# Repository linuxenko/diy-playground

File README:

Yet another bunch of example applications and information about avr programming.
===============================================================================

I've decided to gather everything that interested me in avr programming
inside of a single repository to share it. While I'm learning different
techniques and tricks playing around with avr, the repository is going to grow.

Table of contents
===============================================================================

I'm trying to provide every application with short description in README file,
as well, an information could be provided inside of its source code files.

  documentation  This folder contains some related documentation and things I'm unable to remember, so, now it
  is the place to search instead of making another web search request.

  74hc164     A very basic implementation of "shiftOut" for AVR with example.
  blink-int   The same application using avr timer with interruption.
  blink-timer Custom timer countdown check inside of main loop.
  blink       General "hello world" application for microcontrollers in particular for an avr controller.
  buttons     Button related examples
  pcm-sound   Example of an avr timer usage to play sound using nothing but Mk.
  uart        Serial communication techniques and examples
  usb-pcm     Plays stream (actualy sound data) via usb.

Notes about "electronics" and "documentation" folders:
 Nothing yet

Notes
===============================================================================

Makefiles were borrowed form the v-usb project, they have to be configured for an
exact hardware you're intended to build it for (device type, oscillator frequency,
fuses and maybe avrdude's staff to make "make program" work properly").

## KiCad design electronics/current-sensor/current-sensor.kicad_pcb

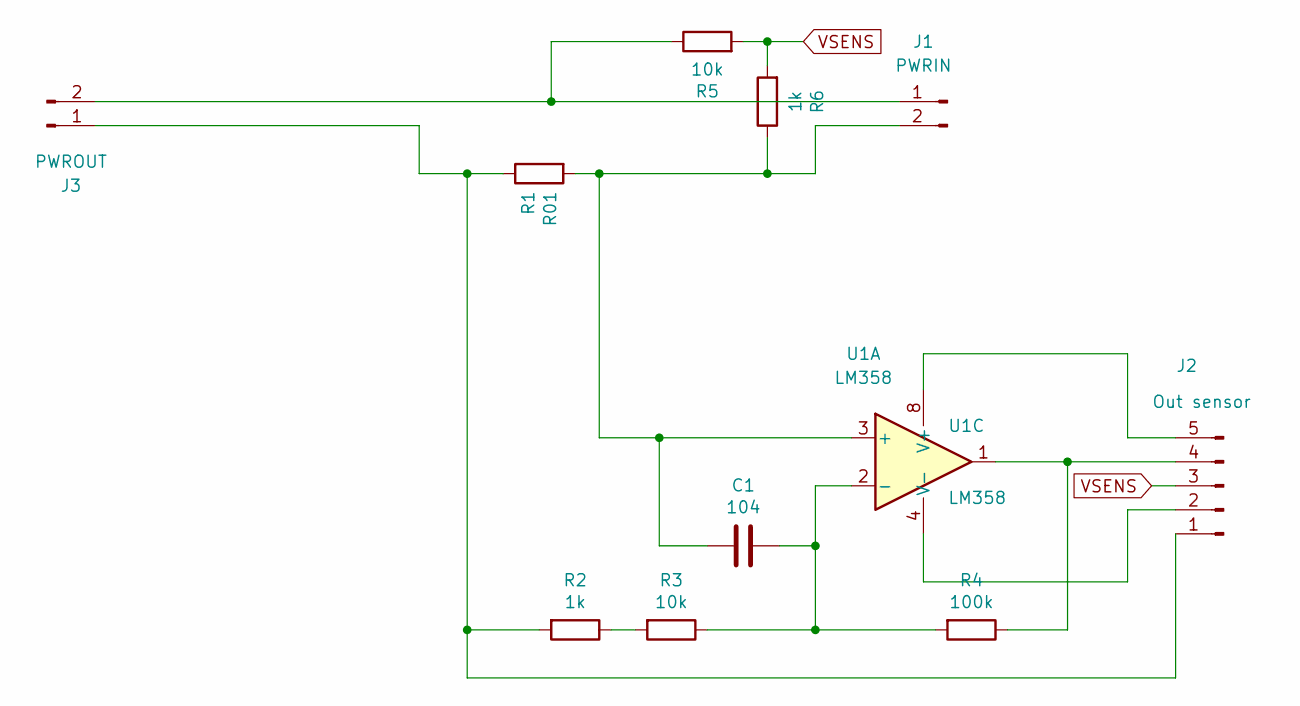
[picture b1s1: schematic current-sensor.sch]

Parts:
C1: 104; C_Disc_D4.3mm_W1.9mm_P5.00mm
J1: PWRIN; PhoenixContact_MCV_1,5_2-G-5.08_1x02_P5.08mm_Vertical
J2: Out sensor; PinHeader_1x05_P2.54mm_Vertical
J3: PWROUT; PhoenixContact_MCV_1,5_2-G-5.08_1x02_P5.08mm_Vertical
R1: R01; R_Axial_DIN0207_L6.3mm_D2.5mm_P10.16mm_Horizontal
R2, R6: 1k; R_Axial_DIN0204_L3.6mm_D1.6mm_P7.62mm_Horizontal
R3, R5: 10k; R_Axial_DIN0204_L3.6mm_D1.6mm_P7.62mm_Horizontal
R4: 100k; R_Axial_DIN0204_L3.6mm_D1.6mm_P7.62mm_Horizontal
U1: LM358; SO-8_5.3x6.2mm_P1.27mm

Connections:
unnamed: C1.1, R3.1, R4.2, U1.2 (-)
unnamed: C1.2, J1.2, R1.2, R6.1, U1.3 (+)
unnamed: J1.1, J3.2, R5.1
unnamed: J2.1, J3.1, R1.1, R2.2
unnamed: J2.2, U1.4 (V-)
unnamed: J2.4, R4.1, U1.1
unnamed: J2.5, U1.8 (V+)
unnamed: R2.1, R3.2
VSENS: J2.3, R5.2, R6.2

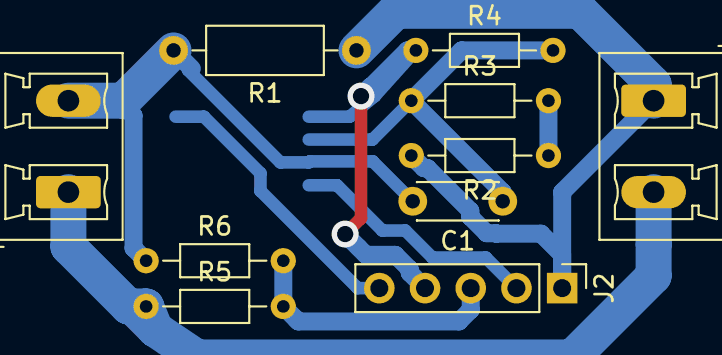
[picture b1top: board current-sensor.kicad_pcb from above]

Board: 2 copper layers, 11 parts (1 on the bottom side), 9 nets.

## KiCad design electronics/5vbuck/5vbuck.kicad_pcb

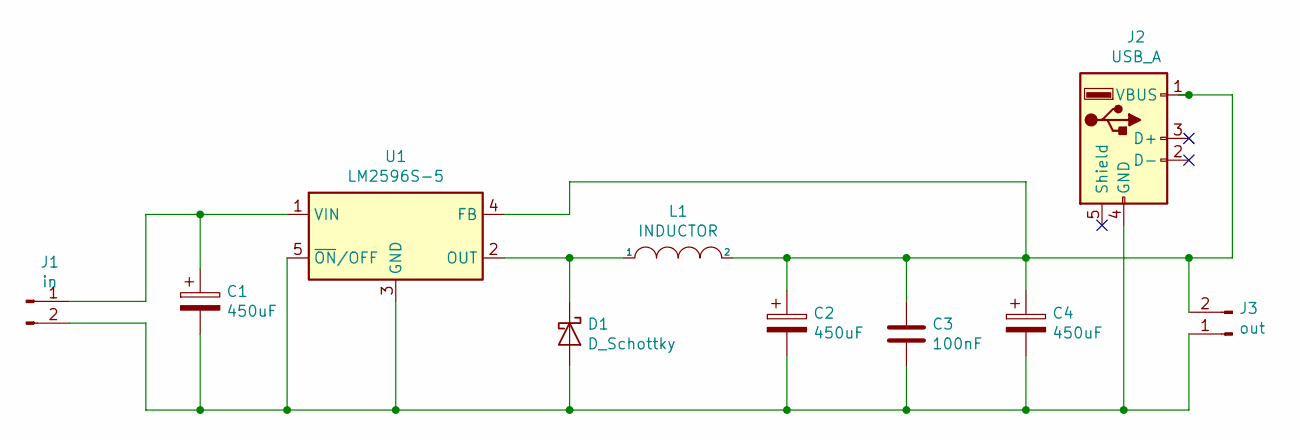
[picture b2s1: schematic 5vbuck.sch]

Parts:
C1, C2, C4: 450uF; CP_Radial_D8.0mm_P5.00mm
C3: 100nF; C_Disc_D4.3mm_W1.9mm_P5.00mm
D1: D_Schottky; D_DO-15_P15.24mm_Horizontal
J1: in; PhoenixContact_MCV_1,5_2-G-5.08_1x02_P5.08mm_Vertical
J2: USB_A; USB_A_Stewart_SS-52100-001_Horizontal
J3: out; PhoenixContact_MCV_1,5_2-G-5.08_1x02_P5.08mm_Vertical
L1: INDUCTOR; L_Toroid_Horizontal_D7.8mm_P13.00mm_Diameter9-5mm_Amidon-T30
U1: LM2596S-5; TO-263-5_TabPin3

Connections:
unnamed: C1.1, J1.1, U1.1 (VIN)
unnamed: C1.2, C2.2, C3.2, C4.2, D1.2 (A), J1.2, J2.4 (GND), J3.1, U1.3 (GND), U1.5 (~ON~/OFF)
unnamed: C2.1, C3.1, C4.1, J2.1 (VBUS), J3.2, L1.2, U1.4 (FB)
unnamed: D1.1 (K), L1.1, U1.2 (OUT)

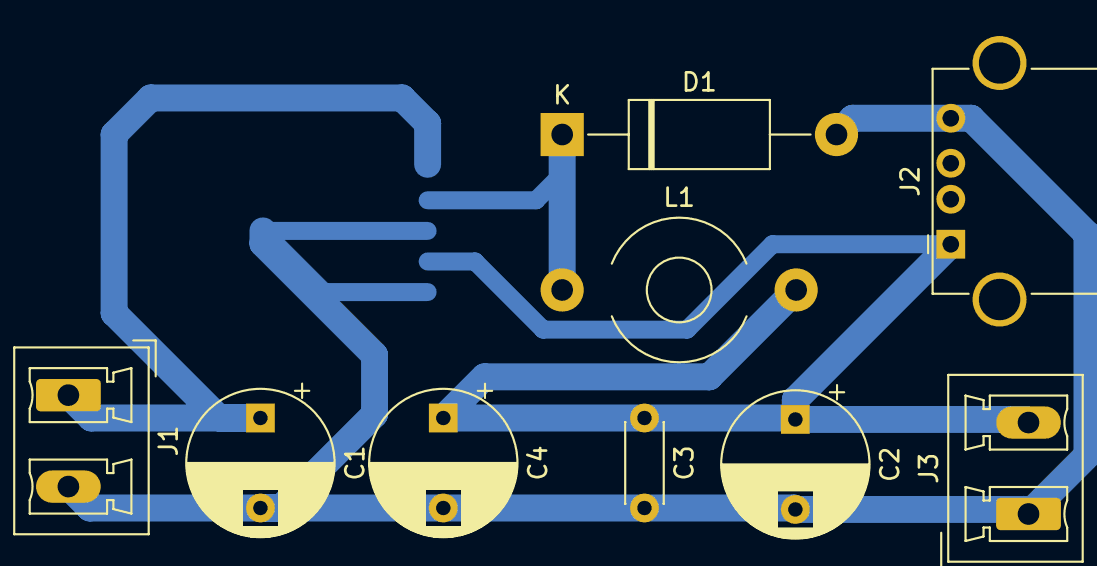
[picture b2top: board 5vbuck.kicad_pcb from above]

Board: 2 copper layers, 10 parts (1 on the bottom side), 4 nets.

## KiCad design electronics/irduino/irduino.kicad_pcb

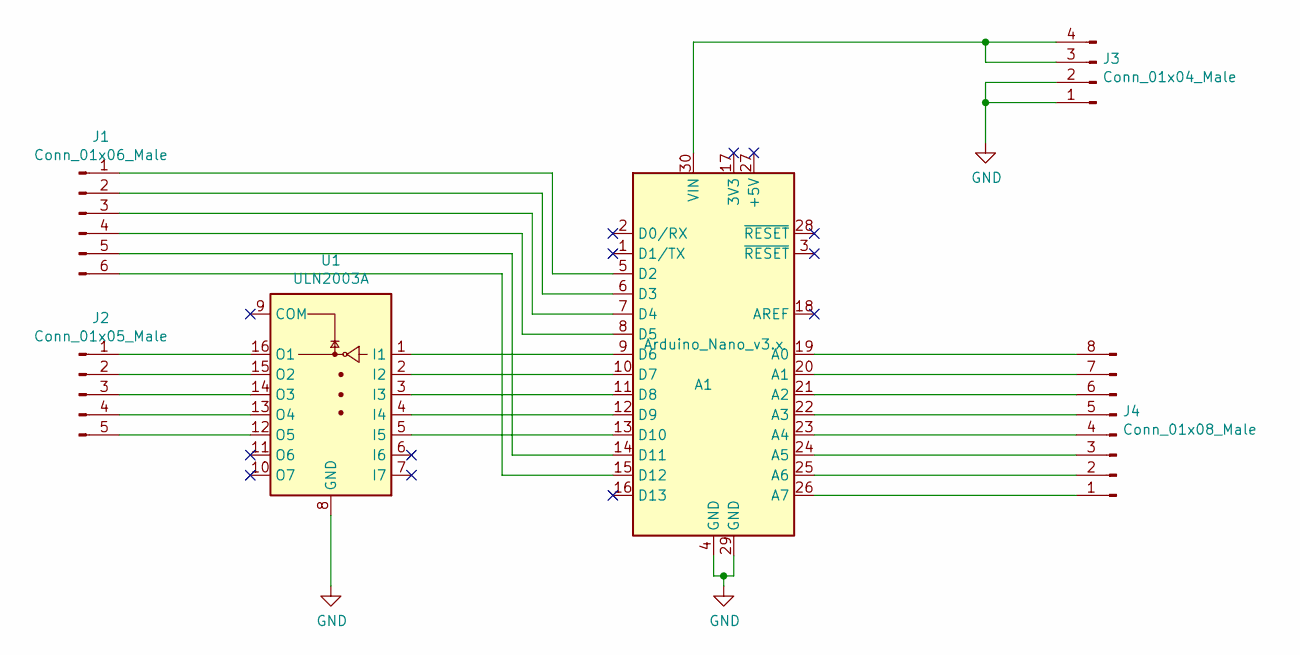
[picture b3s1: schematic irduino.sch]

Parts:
A1: Arduino_Nano_v3.x; Arduino_Nano
J1: Conn_01x06_Male; PinHeader_1x06_P2.54mm_Vertical
J2: Conn_01x05_Male; PinHeader_1x05_P2.54mm_Vertical
J3: Conn_01x04_Male; PinHeader_1x04_P2.54mm_Vertical
J4: Conn_01x08_Male; PinHeader_1x08_P2.54mm_Vertical
U1: ULN2003A; SOIC-16_4.55x10.3mm_P1.27mm

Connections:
GND: A1.4 (GND), A1.29 (GND), J3.1, J3.2, U1.8 (GND)
unnamed: A1.5 (D2), J1.1
unnamed: A1.6 (D3), J1.2
unnamed: A1.7 (D4), J1.3
unnamed: A1.8 (D5), J1.4
unnamed: A1.9 (D6), U1.1 (I1)
unnamed: A1.10 (D7), U1.2 (I2)
unnamed: A1.11 (D8), U1.3 (I3)
unnamed: A1.12 (D9), U1.4 (I4)
unnamed: A1.13 (D10), U1.5 (I5)
unnamed: A1.14 (D11), J1.5
unnamed: A1.15 (D12), J1.6
unnamed: A1.19 (A0), J4.8
unnamed: A1.20 (A1), J4.7
unnamed: A1.21 (A2), J4.6
unnamed: A1.22 (A3), J4.5
unnamed: A1.23 (A4), J4.4
unnamed: A1.24 (A5), J4.3
unnamed: A1.25 (A6), J4.2
unnamed: A1.26 (A7), J4.1
unnamed: A1.30 (VIN), J3.3, J3.4
unnamed: J2.1, U1.16 (O1)
unnamed: J2.2, U1.15 (O2)
unnamed: J2.3, U1.14 (O3)
unnamed: J2.4, U1.13 (O4)
unnamed: J2.5, U1.12 (O5)

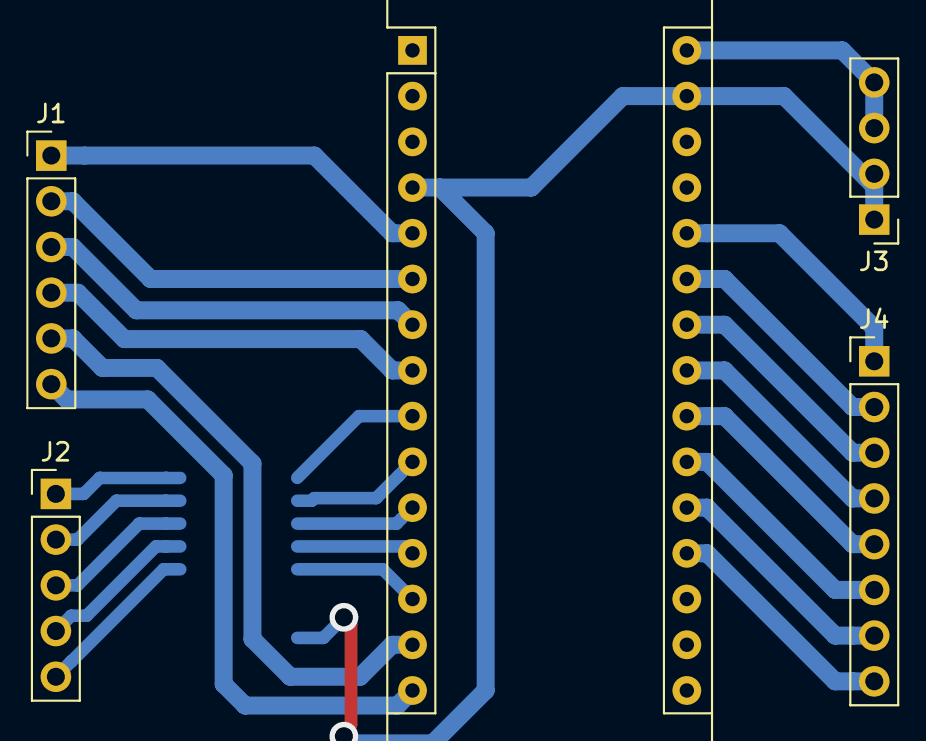
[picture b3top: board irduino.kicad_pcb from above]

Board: 2 copper layers, 6 parts (1 on the bottom side), 26 nets.

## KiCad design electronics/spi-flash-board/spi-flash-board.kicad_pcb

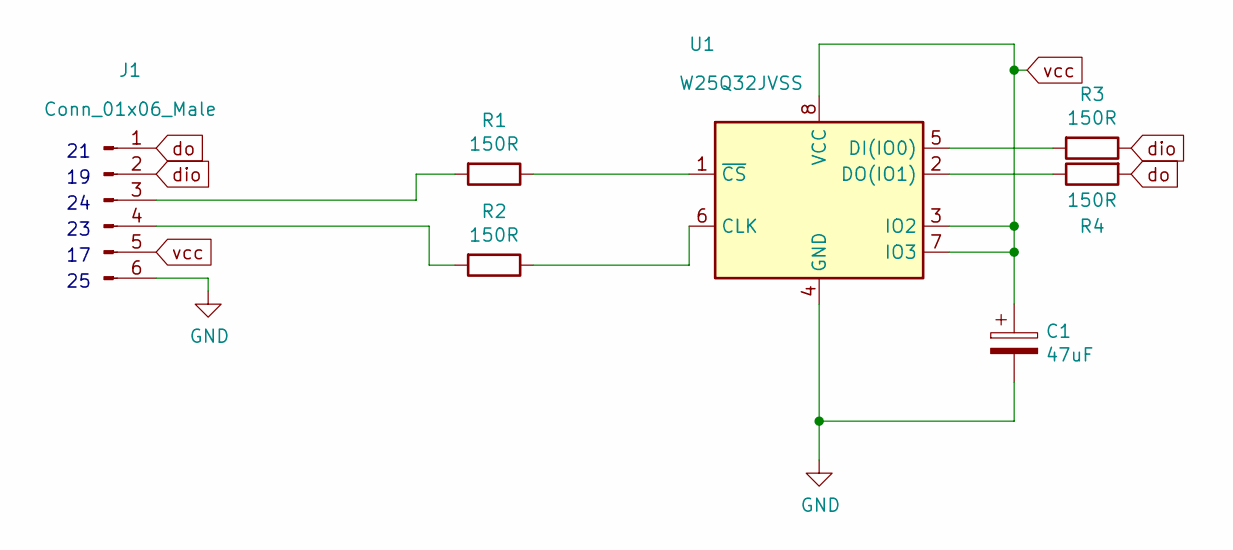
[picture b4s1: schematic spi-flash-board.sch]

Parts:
C1: 47uF; CP_Radial_D8.0mm_P3.80mm
J1: Conn_01x06_Male; PinHeader_1x06_P2.54mm_Vertical
R1, R2, R3, R4: 150R; R_Axial_DIN0204_L3.6mm_D1.6mm_P7.62mm_Horizontal
U1: W25Q32JVSS; SOIC-8_5.23x5.23mm_P1.27mm

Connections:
GND: C1.2, J1.6, U1.4 (GND)
unnamed: J1.3, R1.2
unnamed: J1.4, R2.2
unnamed: R1.1, U1.1 (~CS)
unnamed: R2.1, U1.6 (CLK)
unnamed: R3.2, U1.5 (DI(IO0))
unnamed: R4.1, U1.2 (DO(IO1))
dio: J1.2, R3.1
do: J1.1, R4.2
vcc: C1.1, J1.5, U1.3 (IO2), U1.7 (IO3), U1.8 (VCC)

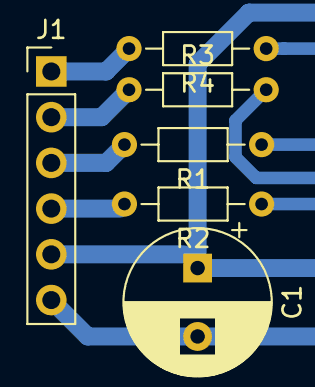
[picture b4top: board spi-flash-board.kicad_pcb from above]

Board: 2 copper layers, 7 parts (1 on the bottom side), 10 nets.

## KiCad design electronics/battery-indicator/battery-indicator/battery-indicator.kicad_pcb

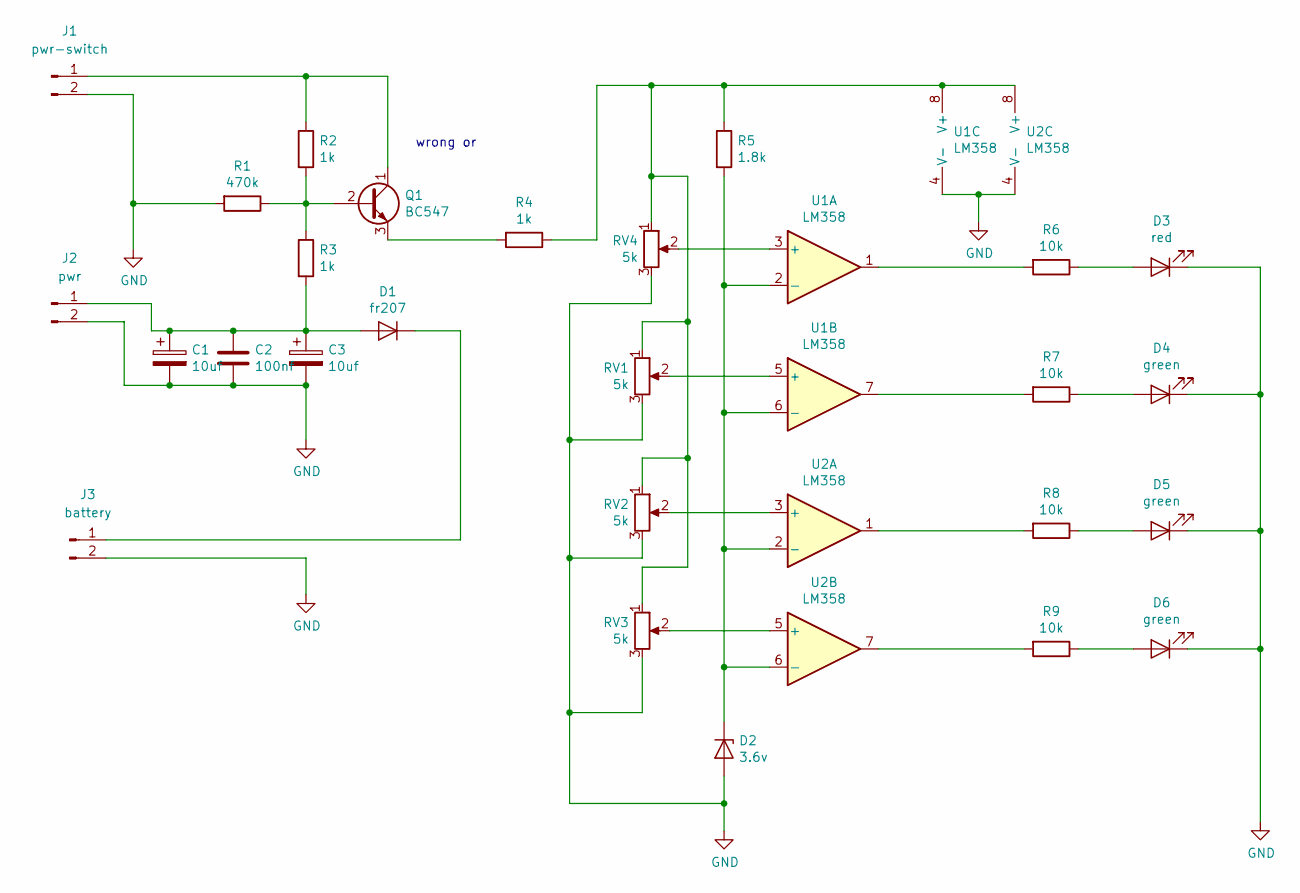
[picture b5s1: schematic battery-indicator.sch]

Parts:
C1, C3: 10uf; CP_Radial_D8.0mm_P3.80mm
C2: 100nf; C_Disc_D5.1mm_W3.2mm_P5.00mm
D1: fr207; D_A-405_P12.70mm_Horizontal
D2: 3.6v; D_A-405_P10.16mm_Horizontal
D3: red; LED_D3.0mm
D4, D5, D6: green; LED_D3.0mm
J1: pwr-switch; PhoenixContact_MCV_1,5_2-G-5.08_1x02_P5.08mm_Vertical
J2: pwr; PhoenixContact_MCV_1,5_2-G-5.08_1x02_P5.08mm_Vertical
J3: battery; PhoenixContact_MCV_1,5_2-G-5.08_1x02_P5.08mm_Vertical
Q1: BC547; TO-92L_Inline_Wide
R1: 470k; R_Axial_DIN0204_L3.6mm_D1.6mm_P7.62mm_Horizontal
R2, R3, R4: 1k; R_Axial_DIN0204_L3.6mm_D1.6mm_P7.62mm_Horizontal
R5: 1.8k; R_Axial_DIN0204_L3.6mm_D1.6mm_P7.62mm_Horizontal
R6, R7, R8, R9: 10k; R_Axial_DIN0204_L3.6mm_D1.6mm_P7.62mm_Horizontal
RV1, RV2, RV3, RV4: 5k; Potentiometer_ACP_CA9-H5_Horizontal
U1, U2: LM358; SOP-8_3.9x4.9mm_P1.27mm

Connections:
GND: C1.2, C2.2, C3.2, D2.2 (A), D3.1 (K), D4.1 (K), D5.1 (K), D6.1 (K), J1.2, J2.2, J3.2, R1.2, RV1.3, RV2.3, RV3.3, RV4.3, U1.4 (V-), U2.4 (V-)
unnamed: C1.1, C2.1, C3.1, D1.2 (A), J2.1, R3.2
unnamed: D1.1 (K), J3.1
unnamed: D2.1 (K), R5.2, U1.2 (-), U1.6 (-), U2.2 (-), U2.6 (-)
unnamed: D3.2 (A), R6.1
unnamed: D4.2 (A), R7.1
unnamed: D5.2 (A), R8.1
unnamed: D6.2 (A), R9.1
unnamed: J1.1, Q1.1 (C), R2.1
unnamed: Q1.2 (B), R1.1, R2.2, R3.1
unnamed: Q1.3 (E), R4.2
unnamed: R4.1, R5.1, RV1.1, RV2.1, RV3.1, RV4.1, U1.8 (V+), U2.8 (V+)
unnamed: R6.2, U1.1
unnamed: R7.2, U1.7
unnamed: R8.2, U2.1
unnamed: R9.2, U2.7
unnamed: RV1.2, U1.5 (+)
unnamed: RV2.2, U2.3 (+)
unnamed: RV3.2, U2.5 (+)
unnamed: RV4.2, U1.3 (+)

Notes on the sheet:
wrong or

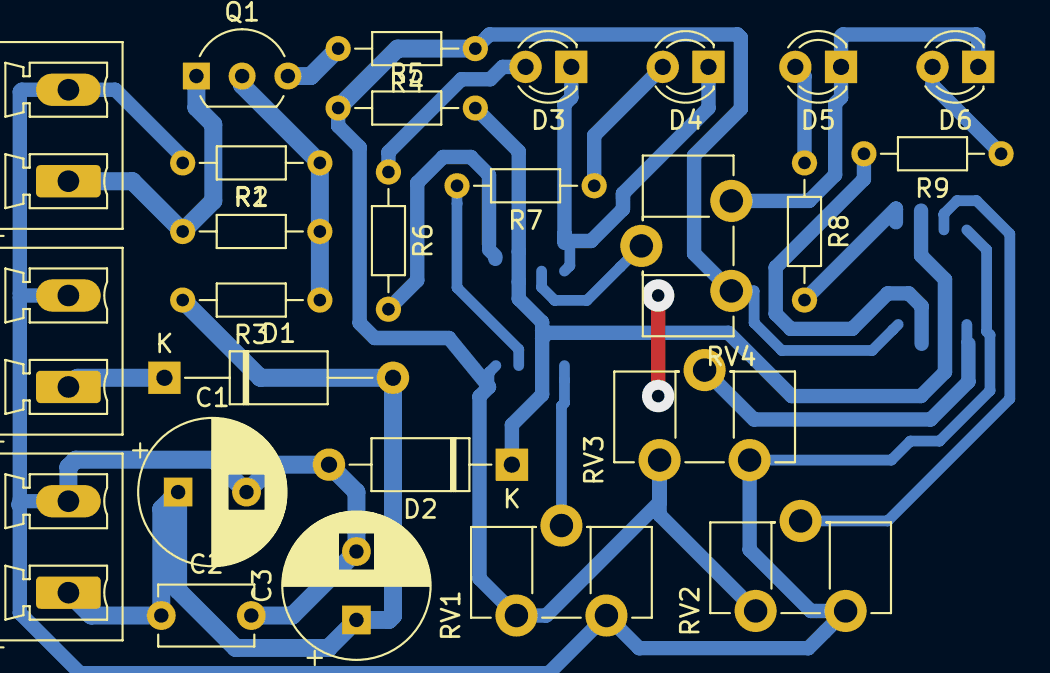
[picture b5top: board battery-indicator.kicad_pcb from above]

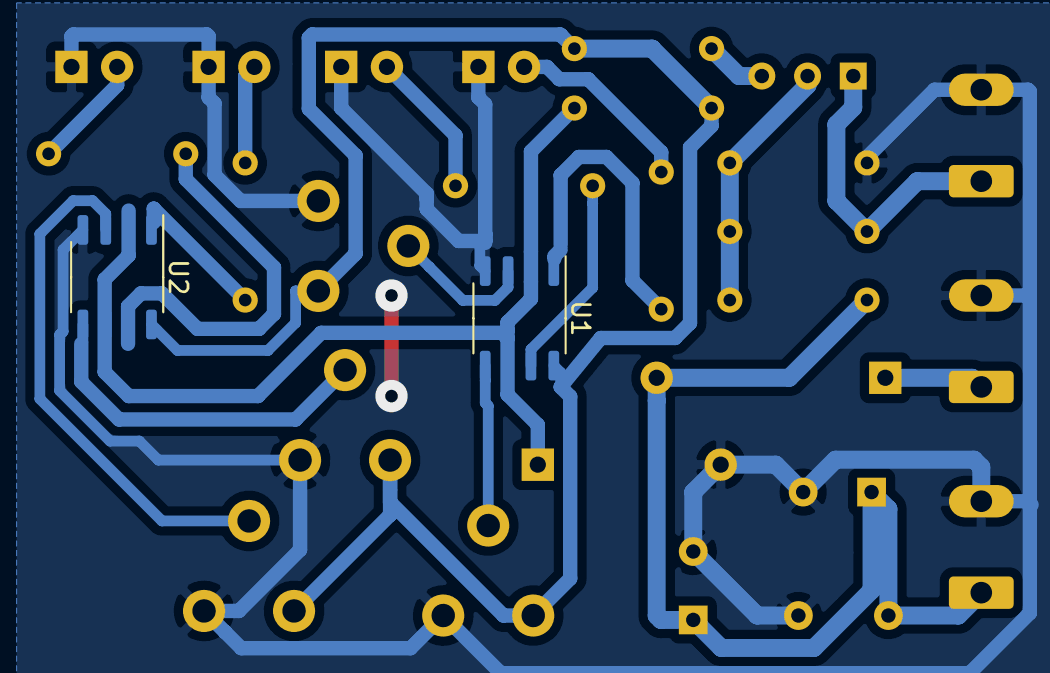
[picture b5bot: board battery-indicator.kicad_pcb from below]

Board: 2 copper layers, 28 parts (2 on the bottom side), 20 nets.

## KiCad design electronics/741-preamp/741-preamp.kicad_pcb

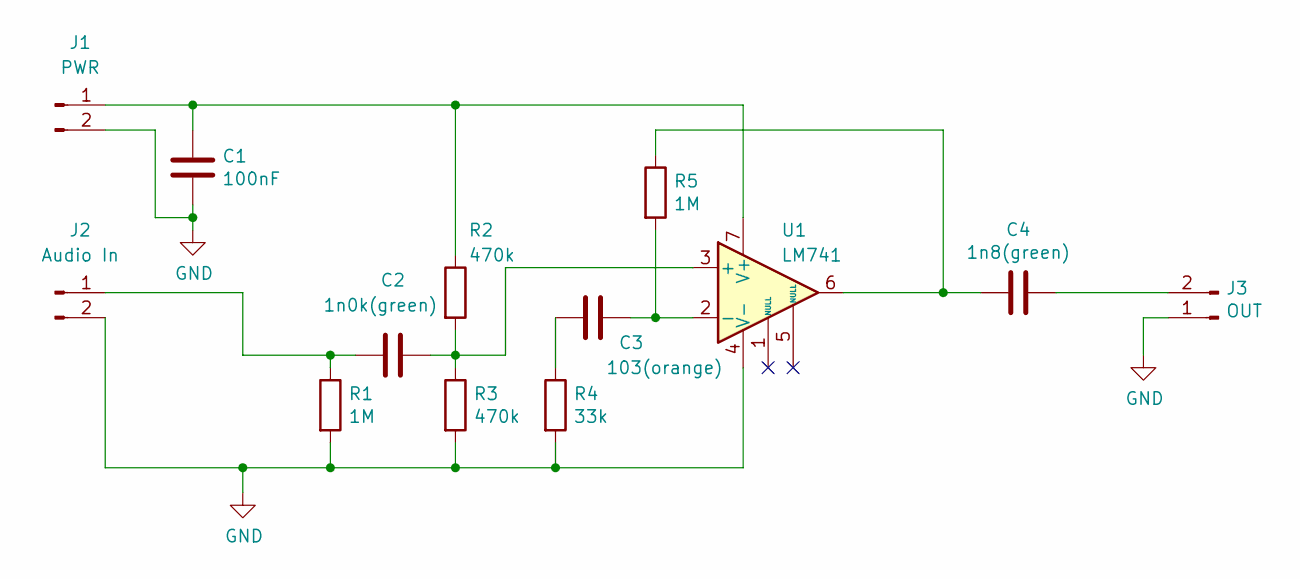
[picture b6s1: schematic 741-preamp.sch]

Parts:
C1: 100nF; C_Disc_D4.3mm_W1.9mm_P5.00mm
C2: 1n0k(green); C_Disc_D4.3mm_W1.9mm_P5.00mm
C3: 103(orange); C_Disc_D4.3mm_W1.9mm_P5.00mm
C4: 1n8(green); C_Disc_D4.3mm_W1.9mm_P5.00mm
J1: PWR; PhoenixContact_MCV_1,5_2-G-5.08_1x02_P5.08mm_Vertical
J2: Audio In; PhoenixContact_MCV_1,5_2-G-5.08_1x02_P5.08mm_Vertical
J3: OUT; PhoenixContact_MCV_1,5_2-G-5.08_1x02_P5.08mm_Vertical
R1, R5: 1M; R_Axial_DIN0204_L3.6mm_D1.6mm_P7.62mm_Horizontal
R2, R3: 470k; R_Axial_DIN0204_L3.6mm_D1.6mm_P7.62mm_Horizontal
R4: 33k; R_Axial_DIN0204_L3.6mm_D1.6mm_P7.62mm_Horizontal
U1: LM741; DIP-8_W7.62mm

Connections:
GND: C1.1, J1.2, J2.2, J3.1, R1.2, R3.2, R4.2, U1.4 (V-)
unnamed: C1.2, J1.1, R2.1, U1.7 (V+)
unnamed: C2.1, R2.2, R3.1, U1.3 (+)
unnamed: C2.2, J2.1, R1.1
unnamed: C3.1, R5.2, U1.2 (-)
unnamed: C3.2, R4.1
unnamed: C4.1, J3.2
unnamed: C4.2, R5.1, U1.6

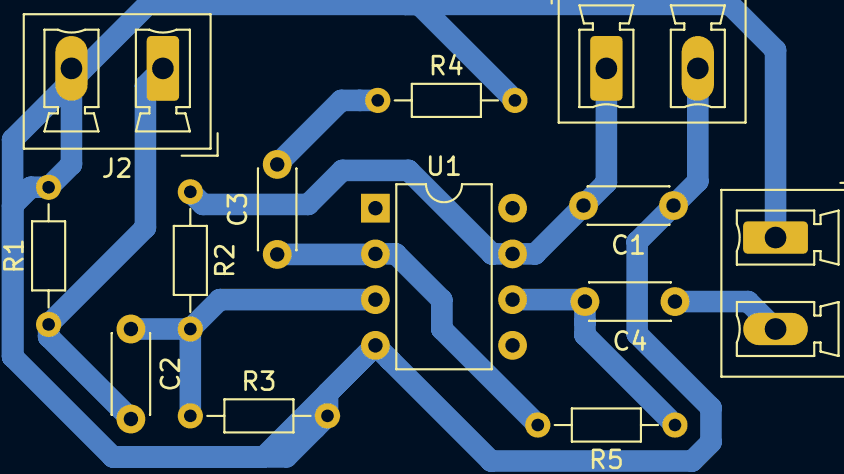
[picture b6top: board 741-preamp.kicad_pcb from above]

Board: 2 copper layers, 13 parts (0 on the bottom side), 8 nets.

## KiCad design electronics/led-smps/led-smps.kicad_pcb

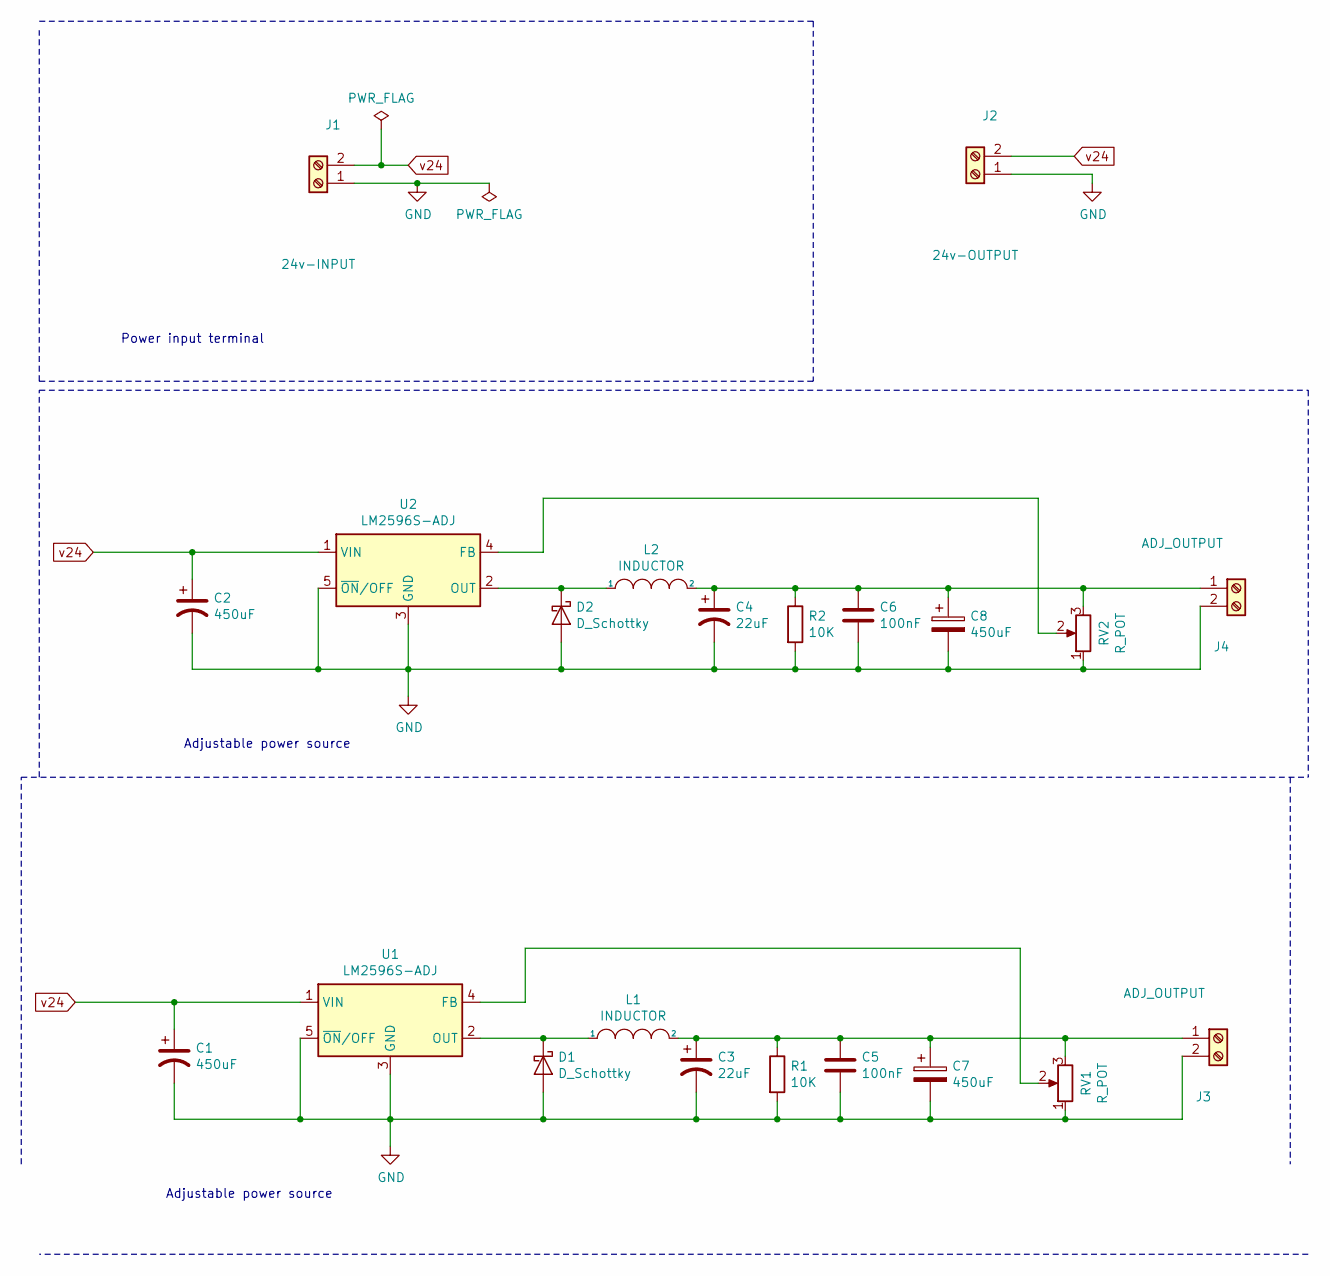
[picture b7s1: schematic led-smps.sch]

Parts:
C1, C2, C7, C8: 450uF; CP_Radial_D8.0mm_P3.50mm
C3, C4: 22uF; CP_Radial_D8.0mm_P3.50mm
C5, C6: 100nF; C_Disc_D4.3mm_W1.9mm_P5.00mm
D1, D2: D_Schottky; D_A-405_P10.16mm_Horizontal
J1: 24v-INPUT; PhoenixContact_MCV_1,5_2-G-3.81_1x02_P3.81mm_Vertical
J2: 24v-OUTPUT; PhoenixContact_MCV_1,5_2-G-3.81_1x02_P3.81mm_Vertical
J3, J4: ADJ_OUTPUT; PhoenixContact_MCV_1,5_2-G-3.81_1x02_P3.81mm_Vertical
L1, L2: INDUCTOR; L_Toroid_Horizontal_D6.5mm_P10.00mm_Diameter7-5mm_Amidon-T25
R1, R2: 10K; R_Axial_DIN0207_L6.3mm_D2.5mm_P10.16mm_Horizontal
RV1, RV2: R_POT; Potentiometer_Piher_PC-16_Single_Horizontal
U1, U2: LM2596S-ADJ; TO-263-5_TabPin3

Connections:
GND: C1.2, C2.2, C3.2, C4.2, C5.2, C6.2, C7.2, C8.2, D1.2 (A), D2.2 (A), J1.1, J2.1, J3.2, J4.2, R1.2, R2.2, RV1.1, RV2.1, U1.3 (GND), U1.5 (~ON~/OFF), U2.3 (GND), U2.5 (~ON~/OFF)
unnamed: C3.1, C5.1, C7.1, J3.1, L1.2, R1.1, RV1.3
unnamed: C4.1, C6.1, C8.1, J4.1, L2.2, R2.1, RV2.3
unnamed: D1.1 (K), L1.1, U1.2 (OUT)
unnamed: D2.1 (K), L2.1, U2.2 (OUT)
unnamed: RV1.2, U1.4 (FB)
unnamed: RV2.2, U2.4 (FB)
v24: C1.1, C2.1, J1.2, J2.2, U1.1 (VIN), U2.1 (VIN)

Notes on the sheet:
Adjustable power source
Power input terminal

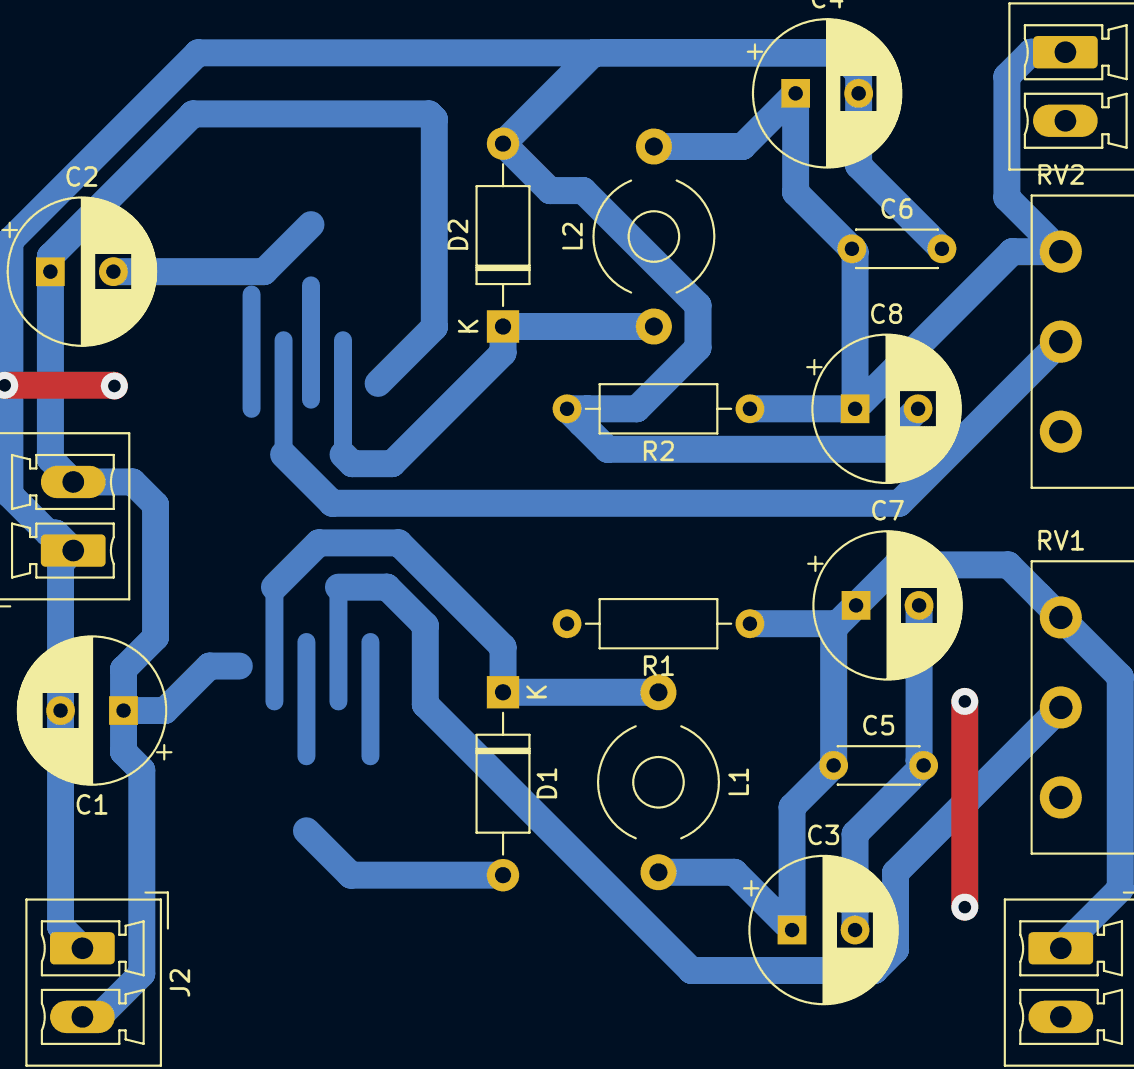
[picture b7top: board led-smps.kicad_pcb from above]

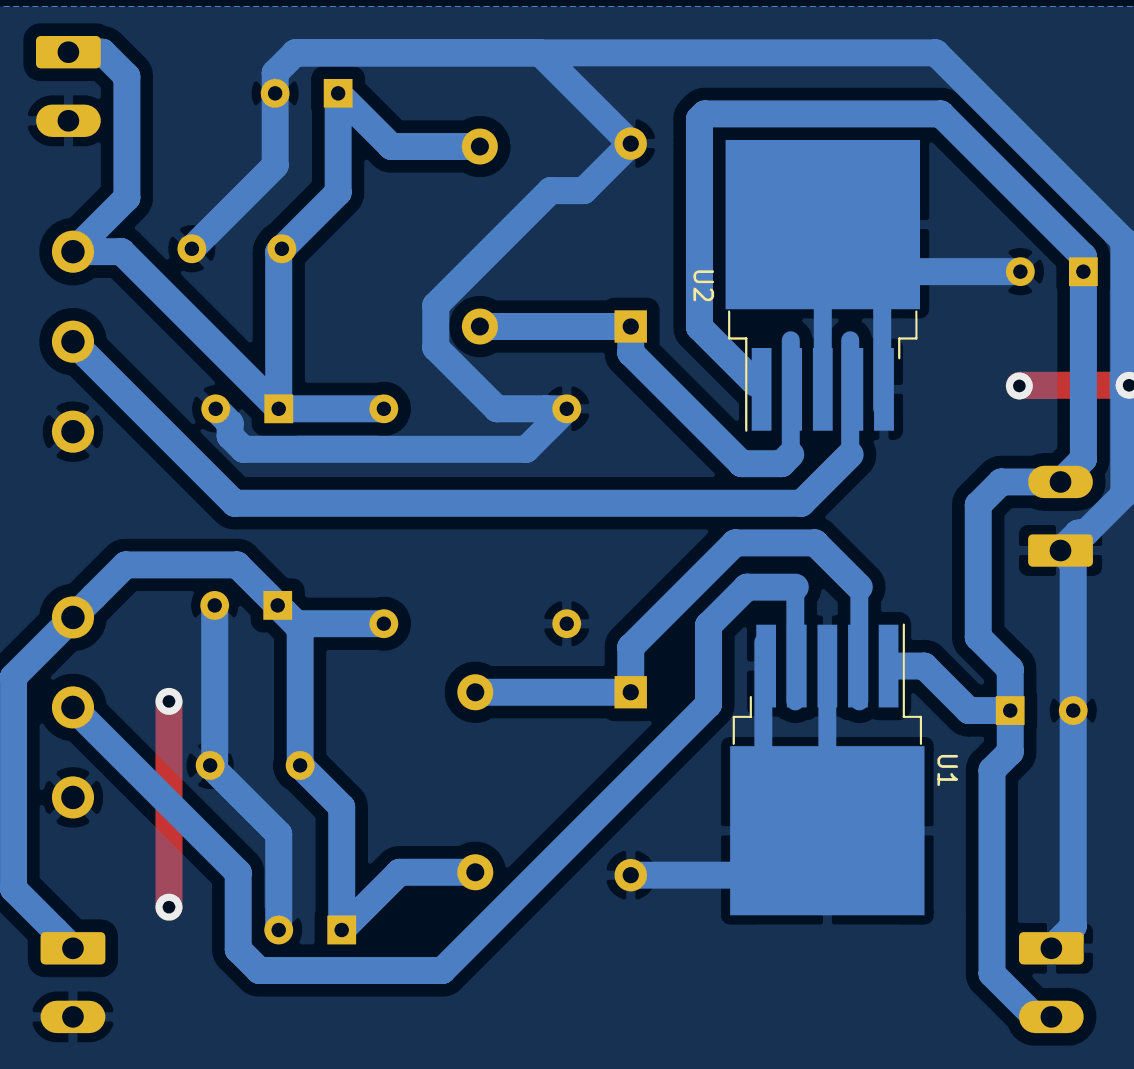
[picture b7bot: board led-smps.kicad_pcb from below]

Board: 2 copper layers, 22 parts (2 on the bottom side), 8 nets.

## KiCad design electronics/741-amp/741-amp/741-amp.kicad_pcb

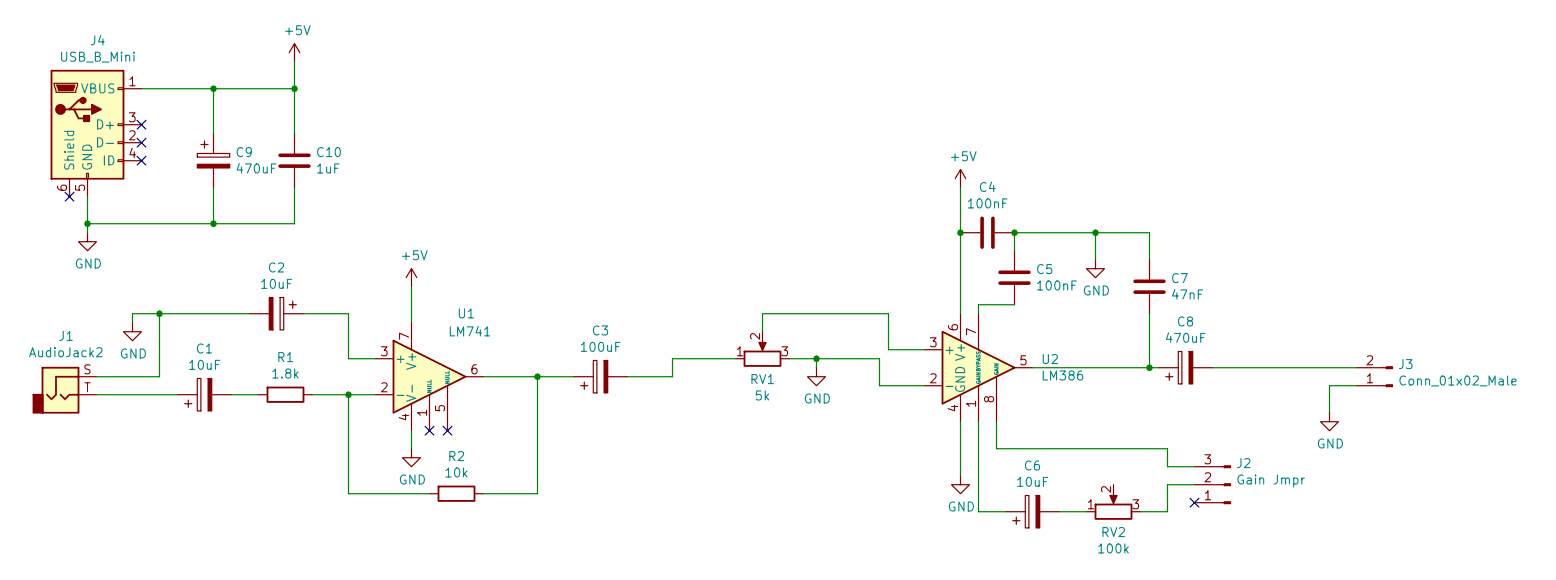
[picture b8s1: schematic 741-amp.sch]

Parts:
C1, C2, C6: 10uF; CP_Radial_D5.0mm_P2.50mm
C3: 100uF; CP_Radial_D6.3mm_P2.50mm
C4, C5: 100nF; C_Disc_D3.8mm_W2.6mm_P2.50mm
C7: 47nF; C_Disc_D3.8mm_W2.6mm_P2.50mm
C8, C9: 470uF; CP_Radial_D6.3mm_P2.50mm
C10: 1uF; C_Disc_D3.8mm_W2.6mm_P2.50mm
J1: AudioJack2; js-211
J2: Gain Jmpr; PinHeader_1x03_P2.54mm_Vertical
J3: Conn_01x02_Male; PinHeader_1x02_P2.54mm_Vertical
J4: USB_B_Mini; USB_Micro_1_27x5
R1: 1.8k; R_Axial_DIN0204_L3.6mm_D1.6mm_P7.62mm_Horizontal
R2: 10k; R_Axial_DIN0204_L3.6mm_D1.6mm_P7.62mm_Horizontal
RV1: 5k; Potentiometer_Piher_T-16H_Single_Horizontal
RV2: 100k; Potentiometer_Piher_T-16H_Single_Horizontal
U1: LM741; SO-8_3.9x4.9mm_P1.27mm
U2: LM386; SO-8_3.9x4.9mm_P1.27mm

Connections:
+5V: C4.2, C9.1, C10.1, J4.1 (VBUS), U1.7 (V+), U2.6 (V+)
GND: C2.2, C4.1, C5.1, C7.1, C9.2, C10.2, J1.S, J3.1, J4.5 (GND), RV1.3, U1.4 (V-), U2.2 (-), U2.4 (GND)
unnamed: C1.1, J1.T
unnamed: C1.2, R1.2
unnamed: C2.1, U1.3 (+)
unnamed: C3.1, R2.1, U1.6
unnamed: C3.2, RV1.1
unnamed: C5.2, U2.7 (BYPASS)
unnamed: C6.1, U2.1 (GAIN)
unnamed: C6.2, RV2.1
unnamed: C7.2, C8.1, U2.5
unnamed: C8.2, J3.2
unnamed: J2.2, RV2.3
unnamed: J2.3, U2.8 (GAIN)
unnamed: R1.1, R2.2, U1.2 (-)
unnamed: RV1.2, U2.3 (+)

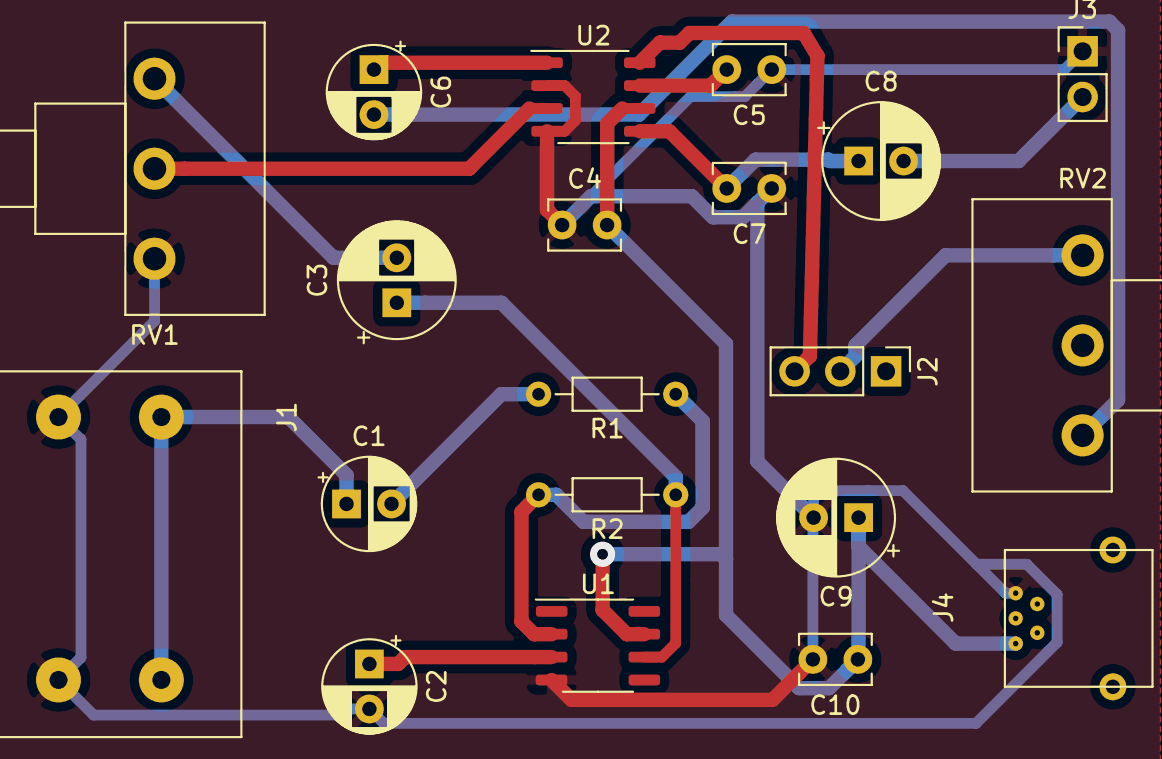
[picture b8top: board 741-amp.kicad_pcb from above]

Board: 2 copper layers, 20 parts (0 on the bottom side), 16 nets.

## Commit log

2019-08-28 General IO staff without any docs
2019-08-28 Datasheed with pinout diagram for atmega8
2019-08-28 A note about Makefiles
2019-08-28 PCM player example
2019-08-28 Ignore uncleaned staff
2019-08-28 blink-int example description
2019-08-28 Timers tutorial for atmega8
2019-08-28 TOC for folders
2019-08-28 Typos fix
2019-08-28 blink-timer example
2019-08-28 Documentation for timers
2019-08-29 usb-pcm application
2019-08-30 Interruption vectors table
2019-09-07 74hc164 usage example
2019-09-07 74hc164 TOC
2019-09-08 Improved "shift" routine
2019-09-08 Try to make it work with hc164
2019-09-08 Shift register with reset support
2019-09-08 Sync 74hc164 with fixes
2019-09-09 Polished shift module
2019-09-09 It finaly gets work
2019-09-09 LCD using shift IC with counter example
2019-09-09 Prettier version with two ICs support
2019-09-09 Test with 595
2019-09-10 Attiny13 blink example
2019-09-19 attiny13 documents
2019-09-20 Uart library documentation
2019-09-20 Uart echo example
2019-09-20 ADC reader example
2019-09-21 Floating point format support example
2019-09-26 Buck converter schematic
2019-09-26 Converter PCB
2019-09-26 Smaller potentiometer tracks
2019-09-28 A little bit structurized docs section
2019-09-28 Interesting code just a copy
2019-09-28 Updated TOC
2019-09-28 Another interesting example
2019-09-28 TOC update buttons
2019-09-28 Circuit for oscilloscope's buffer
2019-10-01 UsbAsp minimal version
2019-10-02 Attiny13 Makefile options for orhodoxal usbasp
2019-10-02 usbasp missing files
2019-10-02 Square wave generator
2019-10-06 Simple lcd hello world for testing purposes
2019-10-06 ttester original code
2019-10-06 Uart library for the project
2019-10-06 Ignore firmware binaries
2019-10-06 Switchable debug mode
2019-10-06 Pretty difinitions
2019-10-06 A try to debug EEPROM strings
2019-10-06 No eeprom strings for debug
2019-10-06 Pretty entrance part
2019-10-06 Diode testing seems to work
2019-10-06 No power modes anymore
2019-10-06 LCD output found
2019-10-06 Restors reference voltage problem
2019-10-06 Resistors depends on reference but works
2019-10-06 Capacitors testing up to 2nF
2019-10-06 Seems like it works
2019-10-06 Seems like ref is fixed now
2019-10-06 Updated ADC
2019-10-07 An own tree for the tt meter
2019-10-07 ic-meter prototype
2019-10-16 pwm backup
2019-10-16 Generator schematic
2019-10-18 mono cable pcb
2019-10-19 Schematic for amp
2019-10-20 Jumpr with empty pin
2019-10-20 Amp's pcb first try
2019-10-27 Bridged version
2019-11-09 led-smps v0a
2019-11-14 preamp schematic
2019-11-17 PCB with connectors
2019-11-17 555 latch simu
2019-11-18 battery-indicator project
2019-11-18 Indicators' schematic
2019-11-21 Indicator but "or" is wrong
2019-11-23 Initial sketch with internal crystal setup
2019-11-25 External ref example
2019-11-26 A bit more accurate reference divider
2020-02-05 Blink optimized
2020-02-05 Actual LCD tester using my m8 16mhz board
2020-02-22 Current adjuster
2020-03-02 adj current driver
2020-03-02 5v buck
2020-03-05 irduino small board design
2020-03-09 Current sensor
2020-03-09 595-liquid initial commit
2020-03-09 LiquidCrystal 595 driver pcb
2020-03-09 png schematic
2020-03-17 Some changes
2020-03-17 Double sensor
2020-03-23 Charge schematic
2020-03-24 PCB design
